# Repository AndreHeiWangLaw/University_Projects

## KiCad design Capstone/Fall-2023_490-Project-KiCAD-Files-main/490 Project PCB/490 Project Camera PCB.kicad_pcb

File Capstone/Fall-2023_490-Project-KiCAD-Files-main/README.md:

# Fall-2023_490-Project-KiCAD-Files
490 Project KiCAD Files

KiCAD doesn't really support git, be careful with your edits.
Try to only push .kd_sch files.

Don't forget to plot/trace your revision in pdf before pushing.

Before merging/rebase to your local branch, check the pdf diagrams for error. 

Don't forget to backup your local branches!

Don't forget to install the ESP32 Library under "/490 Project PCB/CAD Models/ESP32 MCUs/espressif-kicad-addon.zip"
Install it via the KiCAD Package Manager with "Install from File" button.

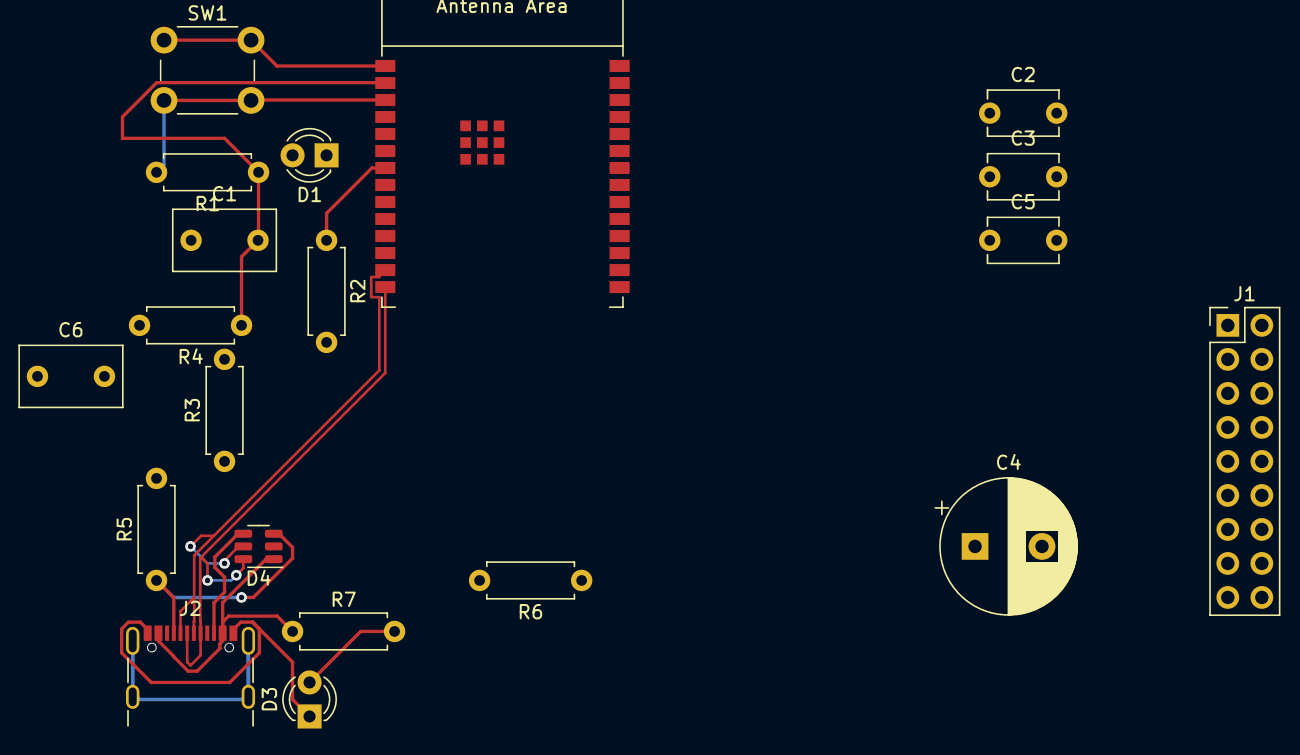
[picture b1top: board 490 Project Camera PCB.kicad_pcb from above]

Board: 2 copper layers, 20 parts (0 on the bottom side), 26 nets.

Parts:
C1, C6: 10u; C_Disc_D7.5mm_W4.4mm_P5.00mm
C2, C5: 0.1u; C_Disc_D5.1mm_W3.2mm_P5.00mm
C3: 1u; C_Disc_D5.1mm_W3.2mm_P5.00mm
C4: 100u; CP_Radial_D10.0mm_P5.00mm
D1: WP7113PGD; LED_D3.0mm
D3: WP7113VBC/D; LED_D3.0mm
D4: SP0503BAHT; SOT-23-6
J1: Conn_01x16; PinHeader_2x09_P2.54mm_Vertical
J2: Molex_2171750001; USB_C_Receptacle_GCT_USB4105-xx-A_16P_TopMnt_Horizontal
R1: 10k; R_Axial_DIN0207_L6.3mm_D2.5mm_P7.62mm_Horizontal
R2: 56R; R_Axial_DIN0207_L6.3mm_D2.5mm_P7.62mm_Horizontal
R3: 200; R_Axial_DIN0207_L6.3mm_D2.5mm_P7.62mm_Horizontal
R4: 392; R_Axial_DIN0207_L6.3mm_D2.5mm_P7.62mm_Horizontal
R5, R6: 5k1; R_Axial_DIN0207_L6.3mm_D2.5mm_P7.62mm_Horizontal
R7: 91R; R_Axial_DIN0207_L6.3mm_D2.5mm_P7.62mm_Horizontal
SW1: D6R90 F1 LFS; SW_PUSH_6mm_H7.3mm
U1: ESP32-C6-WROOM-1

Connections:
+3V3: C1.2 (-), C2.1 (+), C4.1 (+), C5.2 (-), J1.1, R1.1 (+), R3.2 (-), R4.1 (+), U1.2 (3V3)
CAMERA_DATA_1: J1.4, U1.10 (GPIO8)
CAMERA_DATA_2: J1.5, U1.15 (GPIO9)
CAMERA_DATA_3: J1.6, U1.11 (GPIO10)
CAMERA_DATA_4: J1.7, U1.12 (GPIO11)
CAMERA_DATA_5: J1.8, U1.23 (GPIO15)
CAMERA_DATA_6: J1.9, U1.16 (GPIO18)
CAMERA_DATA_7: J1.10, U1.17 (GPIO19)
CAMERA_DATA_8: J1.11, U1.18 (GPIO20)
CAMERA_HREF: J1.15, U1.27 (GPIO2/ADC1_CH2)
CAMERA_PCLK: J1.13, U1.8 (GPIO0/ADC1_CH0/XTAL_32K_P)
CAMERA_SIOC_SCL: J1.3, U1.21 (GPIO23)
CAMERA_SIOC_SDA: J1.2, U1.20 (GPIO22)
CAMERA_VSYNC: J1.12, U1.26 (GPIO3/ADC1_CH3)
CAMERA_XCLK: J1.14, U1.9 (GPIO1/ADC1_CH1/XTAL_32K_N)
GND: C1.1 (+), C2.2 (-), C3.1 (+), C4.2 (-), C5.1 (+), C6.1 (+), D1.1 (K), D3.1 (K), D4.2 (A), J1.16, J2.A1 (GND), J2.A12 (GND), J2.B1 (GND), J2.B12 (GND), R4.2 (-), R5.2 (-), R6.2 (-), SW1.1, U1.1 (GND), U1.28 (GND), U1.29 (GND)
unnamed: C3.2 (-), R1.2 (-), SW1.2, U1.3 (EN/CHIP_PU)
unnamed: C6.2 (-), R3.1 (+)
unnamed: D1.2 (A), R2.2 (-)
unnamed: D3.2 (A), R7.2 (-)
unnamed: D4.3 (K), J2.A5 (CC1), R5.1 (+)
unnamed: D4.4 (K), J2.B5 (CC2), R6.1 (+)
unnamed: R2.1 (+), U1.7 (MTDO/GPIO7)
unnamed: D4.1 (K), J2.A4 (VBUS), J2.A9 (VBUS), J2.B4 (VBUS), J2.B9 (VBUS), R7.1 (+)
USB_D+: D4.6 (K), J2.A6 (D+), J2.B6 (D+), U1.14 (GPIO13/USB_D+)
USB_D-: D4.5 (K), J2.A7 (D-), J2.B7 (D-), U1.13 (GPIO12/USB_D-)

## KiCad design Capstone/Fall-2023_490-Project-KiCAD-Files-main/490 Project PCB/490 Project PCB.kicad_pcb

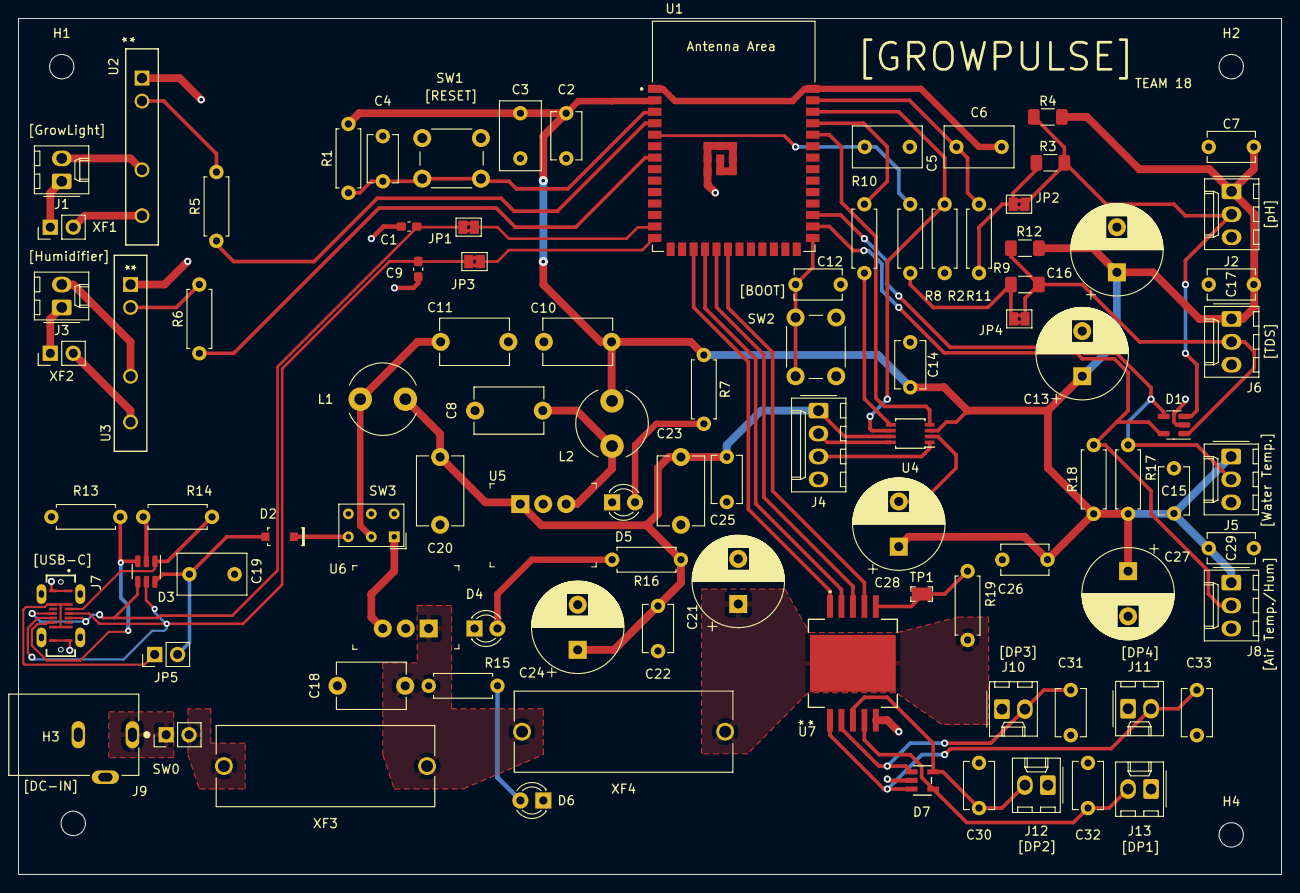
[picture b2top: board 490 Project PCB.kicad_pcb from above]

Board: 2 copper layers, 139.9 x 94.8 mm, 99 parts (0 on the bottom side), 57 nets.

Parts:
C1, C9: 47 pF; C_0603_1608Metric_Pad1.08x0.95mm_HandSolder
C2, C7, C14, C15, C17, C22, C25, C26, C29, C30, C31, C32, C33: 0.1u; C_Disc_D5.1mm_W3.2mm_P5.00mm
C3, C5, C6, C19: 10u; C_Disc_D7.5mm_W4.4mm_P5.00mm
C4, C12: 1u; C_Disc_D5.1mm_W3.2mm_P5.00mm
C8, C10, C11, C18, C20, C23: 22u; C_Disc_D7.5mm_W5.0mm_P7.50mm
C13, C16, C21, C24, C27, C28: 100u; CP_Radial_D10.0mm_P5.00mm
D1: SP0504BAHT; SOT-23-5
D2: 1N5819HW-7-F; SOD-123
D3: SP0503BAHT; SOT-23-6
D4: WP7113VBC/D; LED_D3.0mm
D5: WP7113PGD; LED_D3.0mm
D6: WP7113ID5V; LED_D3.0mm
D7: ESDA14V2SC5; SOT23-5L_STM
H1, H2, H3, H4: MountingHole; MountingHole_2.7mm_M2.5
J1, J3, J10, J11, J12, J13: Molex_0022112022; Molex_KK-254_AE-6410-02A_1x02_P2.54mm_Vertical
J2, J5, J6, J8: Molex_0022112032; Molex_KK-254_AE-6410-03A_1x03_P2.54mm_Vertical
J4: Molex_0022112042; Molex_KK-254_AE-6410-04A_1x04_P2.54mm_Vertical
J7: Molex_2171750001; GCT_USB4120-03-C_REVA
J9: PJ-102A
JP1, JP3: R0; SolderJumper-2_P1.3mm_Bridged2Bar_Pad1.0x1.5mm
JP2, JP4: SolderJumper_2_Closed; SolderJumper-2_P1.3mm_Bridged2Bar_Pad1.0x1.5mm
JP5: Jumper_VBUS_Open; PinHeader_1x02_P2.54mm_Vertical
L1, L2: 10u; L_Radial_D7.8mm_P5.00mm_Fastron_07HCP
R1, R19: 10k; R_Axial_DIN0207_L6.3mm_D2.5mm_P7.62mm_Horizontal
R2: 51k; R_Axial_DIN0207_L6.3mm_D2.5mm_P7.62mm_Horizontal
R3, R4, R9, R12: TBD; R_1206_3216Metric_Pad1.30x1.75mm_HandSolder
R5, R6: 392; R_Axial_DIN0207_L6.3mm_D2.5mm_P7.62mm_Horizontal
R7: 56R; R_Axial_DIN0207_L6.3mm_D2.5mm_P7.62mm_Horizontal
R8, R11: 1k8; R_Axial_DIN0207_L6.3mm_D2.5mm_P7.62mm_Horizontal
R10: 510; R_Axial_DIN0207_L6.3mm_D2.5mm_P7.62mm_Horizontal
R13, R14: 5k1; R_Axial_DIN0207_L6.3mm_D2.5mm_P7.62mm_Horizontal
R15: 560; R_Axial_DIN0207_L6.3mm_D2.5mm_P7.62mm_Horizontal
R16: 91R; R_Axial_DIN0207_L6.3mm_D2.5mm_P7.62mm_Horizontal
R17, R18: 4k7; R_Axial_DIN0207_L6.3mm_D2.5mm_P7.62mm_Horizontal
SW0: PH1-02-UA; PinHeader_1x02_P2.54mm_Vertical
SW1, SW2: D6R90 F1 LFS; SW_PUSH_6mm_H7.3mm
SW3: NKK_GW22LCP; SW_NKK_GW12LJP
TP1: RCT-0C; PROBE_PAD_0805
U1: ESP32-S3-WROOM-1; XCVR_ESP32-S3-WROOM-1-N8R2
U2, U3: CPC1966Y; SIP4_CPC1966Y_LTF
U4: TXB0102DCT; TSSOP-8_3x3mm_P0.65mm
U5: VX7803-1000; 3-SIP_Module_V7805-1000
U6: V7805-2000; 3-SIP_Module_V7805-1000
U7: VN340SPTR-33-E; PowerSO-10_STM
XF1, XF2: PH1-02-UA; PinHeader_1x02_P2.54mm_Vertical
XF3: 3A; FUSE_4628
XF4: 1A; FUSE_4628

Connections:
+3V3: C2.1 (+), C3.2 (-), C7.2 (-), C10.2 (-), C13.1 (+), C14.2 (-), C15.2 (-), C16.1 (+), C17.2 (-), C26.2 (-), C27.1 (+), C28.1 (+), C29.2 (-), J2.1, J5.1, J6.1, J8.1, L2.2, R1.2 (-), R4.1 (+), R7.1 (+), R12.1 (+), R17.1 (+), R18.1 (+), U1.2 (3V3), U4.3 (VCCA)
+5V: C20.2 (-), C22.2 (-), C23.2 (-), C24.1 (+), C25.2 (-), J4.1, L1.2, R16.1 (+), U4.7 (VCCB), U5.1 (Vin+)
+12V: C18.2 (-), R15.1 (+), U6.1 (Vin+), XF3.2, XF4.2
/BOOT: C12.1 (+), SW2.1, U1.27 (GPIO0/BOOT)
/EN_TXB0102D: R2.1 (+), U1.38 (GPIO2/TOUCH2/ADC1_CH1), U4.6 (OE)
/UART0RX: U1.36 (U0RXD/GPIO44/CLK_OUT2), U4.4 (A2)
/UART0TX: R10.2 (-), U1.37 (U0TXD/GPIO43/CLK_OUT1)
ADC-Sensor_pH: JP2.1 (A), R3.1 (+), R11.1 (+)
ADC-TDS_Sensor: JP4.1 (A), R8.1 (+), R9.1 (+)
GND: C1.1 (+), C2.2 (-), C3.1 (+), C4.1 (+), C5.2 (-), C6.2 (-), C7.1 (+), C8.1 (+), C9.1 (+), C10.1 (+), C11.1 (+), C12.2 (-), C13.2 (-), C14.1 (+), C15.1 (+), C16.2 (-), C17.1 (+), C18.1 (+), C19.1 (+), C20.1 (+), C21.2 (-), C22.1 (+), C23.1 (+), C24.2 (-), C25.1 (+), C26.1 (+), C27.2 (-), C28.2 (-), C29.1 (+), C30.1 (+), C31.1 (+), C32.1 (+), C33.1 (+), D1.2 (A), D3.2 (A), D4.1 (K), D5.1 (K), D6.1 (K), D7.2, J2.3, J4.4, J5.3, J6.3, J7.A1 (GND), J7.A12 (GND), J7.B1 (GND), J7.B12 (GND), J8.3, J9.2, J9.3, J10.1, J11.1, J12.1, J13.1, R2.2 (-), R13.2 (-), R14.2 (-), SW1.1, SW2.2, U1.1 (GND), U1.40 (GND), U1.41_1, U1.41_2, U1.41_3, U1.41_4, U1.41_5, U1.41_6, U1.41_7, U1.41_8, U1.41_9, U2.1, U3.1, U4.2 (GND), U5.2 (GND), U6.2 (GND), U7.5 (GND)
GPIO-Relay_Dosing_Pump_01: U1.17 (GPIO9/TOUCH9/ADC1_CH8/FSPIHD/SUBSPIHD), U7.10 (IN1)
GPIO-Relay_Dosing_Pump_02: U1.18 (GPIO10/TOUCH10/ADC1_CH9/FSPICS0/FSPIIO4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), U7.9 (IN2)
GPIO-Relay_Dosing_Pump_03: U1.19 (GPIO11/TOUCH11/ADC2_CH0/FSPID/FSPIIO5/S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), U7.8 (IN3)
GPIO-Relay_Dosing_Pump_04: U1.20 (GPIO12/TOUCH12/ADC2_CH1/FSPICLK/FSPIIO6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), U7.7 (IN4)
GPIO-Relay_Grow_Light: R5.1 (+), U1.4 (GPIO4/TOUCH4/ADC1_CH3)
GPIO-Relay_Main_Pump: R6.1 (+), U1.7 (GPIO7/TOUCH7/ADC1_CH6)
GPIO-Sensor_AirHTemp: D1.5 (K), J8.2, R18.2 (-), U1.28 (SPIIO6/GPIO35/FSPID/SUBSPID)
GPIO-Water_Temperature: D1.4 (K), J5.2, R17.2 (-), U1.29 (SPIIO7/GPIO36/FSPICLK/SUBSPICLK)
unnamed: C4.2 (-), R1.1 (+), SW1.2, U1.3 (EN)
unnamed: C5.1 (+), R8.2 (-), U1.5 (GPIO5/TOUCH5/ADC1_CH4)
unnamed: C6.1 (+), R11.2 (-), U1.39 (GPIO1/TOUCH1/ADC1_CH0)
unnamed: C8.2 (-), L2.1, U5.3 (Vo+)
unnamed: C11.2 (-), L1.1, SW3.2 (B)
unnamed: C19.2 (-), D2.A, D3.6 (K), JP5.2 (B)
unnamed: C21.1 (+), R19.1 (+), U7.EPAD (VCC), XF4.1
unnamed: D4.2 (A), R16.2 (-)
unnamed: D5.2 (A), R7.2 (-)
unnamed: D6.2 (A), R15.2 (-)
unnamed: J1.1, XF1.1 (A)
unnamed: J1.2, U2.3
unnamed: D1.3 (K), J2.2, JP2.2 (B), R3.2 (-), R4.2 (-)
unnamed: J3.1, XF2.1 (A)
unnamed: J3.2, U3.3
unnamed: J4.2, U4.8 (B1)
unnamed: J4.3, U4.1 (B2)
unnamed: D1.1 (K), J6.2, JP4.2 (B), R9.2 (-), R12.2 (-)
unnamed: D3.1 (K), J7.A5 (CC1), R14.1 (+)
unnamed: D3.3 (K), J7.B5 (CC2), R13.1 (+)
unnamed: JP1.1 (A), U1.13 (GPIO19/U1RTS/ADC2_CH8/CLK_OUT2/USB_D-)
unnamed: JP3.1 (A), U1.14 (GPIO20/U1CTS/ADC2_CH9/CLK_OUT1/USB_D+)
unnamed: J7.A4 (VBUS), J7.A9 (VBUS), J7.B4 (VBUS), J7.B9 (VBUS), JP5.1 (A)
unnamed: R5.2 (-), U2.2
unnamed: R6.2 (-), U3.2
unnamed: R10.1 (+), U4.5 (A1)
unnamed: R19.2 (-), TP1.1, U7.6 (DIAG)
unnamed: J9.1, SW0.1 (A)
unnamed: SW0.2 (B), XF3.1
unnamed: SW3.1 (A), U6.3 (Vo+)
unnamed: U2.4, XF1.2 (B)
unnamed: U3.4, XF2.2 (B)
O-PWR_Dosing_Pump_01: C33.2 (-), D7.3, J11.2, U7.1 (OUT1)
O-PWR_Dosing_Pump_02: C31.2 (-), D7.1, J10.2, U7.2 (OUT2)
O-PWR_Dosing_Pump_03: C30.2 (-), D7.5, J12.2, U7.3 (OUT3)
O-PWR_Dosing_Pump_04: C32.2 (-), D7.4, J13.2, U7.4 (OUT4)
USB_D+: C9.2 (-), D3.5 (K), J7.A6 (D+), J7.B6 (D+), JP3.2 (B)
USB_D-: C1.2 (-), D3.4 (K), J7.A7 (D-), J7.B7 (D-), JP1.2 (B)
VBUS: D2.K, SW3.3 (C)

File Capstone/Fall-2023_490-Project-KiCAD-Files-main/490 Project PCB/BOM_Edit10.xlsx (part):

Item | Reference | Description | Value | Qty | Manufacturer | MPN | Package | Type | Supplier | Supplier_PN | Price | Price Ext.
1 | C1, C9 | SMD 1608 Capacitor | 47 pF | 2 | Murata Electronics | GRM1885C1H470JA01D | 0603 (1608 Metric) | SMD | Digikey | 490-1419-2-ND | 0.18000 | 0.36
2 | C2, C7, C14, C15, C17, C22, C25, C29-C33 | THT Radial Capacitor | 0.1u | 12 | Murata Electronics | RDER71H104K0M1H03A | Radial | Tru-Hole | Digikey | 490-9144-1-ND | 0.66000 | 7.92
3 | C3, C5, C6, C19 | THT Radial Capacitor | 10u | 4 | Murata Electronics | RDEC71H106K3S1H03A | Radial | Tru-Hole | Digikey | 490-16957-1-ND | 1.47000 | 5.88
4 | C4, C12 | THT Radial Capacitor | 1u | 2 | Murata Electronics | RDER71H105K2M1H03A | Radial | Tru-Hole | Digikey | 490-9146-1-ND | 0.92000 | 1.84
5 | C8, C10, C11, C18, C20, C23 | THT CER Radial Capacitor | 22u | 6 | TDK Corporation | CC45SL3JD220JYGNA | Radial | Tru-Hole | Digikey | 445-181008-ND | 0.37000 | 2.2199999999999998
6 | C13, C16, C21, C24, C27, C28 | THT ELEC Radial Capacitor | 100u | 6 | Panasonic Electronic Components | EEU-FC1J101 | Radial | Tru-Hole | Digikey | P10343-ND | 0.85000 | 5.0999999999999996
7 | D1 | 4 Channel TVS Module: TVS DIODE 5.5VWM 8.5VC SOT23-5 | SP0504BAHT | 1 | Littelfuse Inc. | SP0504BAHTG | SOT-23-5 | SMD | Digikey | F3157TR-ND | 1.27000 | 1.27
8 | D2 | Diode 40 V 1A Surface Mount SOD-123 | 1N5819HW-7-F | 1 | Diodes Incorporated | 1N5819HW-7-F | SOD-123 | SMD | Digikey | 1N5819HW-FDICT-ND | 0.62000 | 0.62
9 | D3 | 8.5V Clamp Ipp Tvs Diode Surface Mount SOT-143-4 | SP0503BAHT | 1 | Littelfuse Inc. | SP0503BAHTG | SOT-143-4 | SMD | Digikey | F2715TR-ND | 1.24000 | 1.24
10 | D4 | LED Blue: LED BLUE CLEAR T-1 3/4 T/H | WP7113VBC/D | 1 | Kingbright | WP7113VBC/D | Radial | Tru-Hole | Digikey | 754-1807-ND | 0.80000 | 0.8
11 | D5 | LED Green: LED GREEN DIFFUSED T-1 3/4 T/H | WP7113PGD | 1 | Kingbright | WP7113PGD | Radial | Tru-Hole | Digikey | 754-1897-ND | 0.58000 | 0.57999999999999996
12 | D6 | 12V Resistor LED: LED RED CLEAR T-1 T/H | WP7113ID5V | 1 | Kingbright | WP7113ID5V | Radial | Tru-Hole | Digikey | LTH3MM12VFR4100-ND | 1.78000 | 1.78
13 | D7 | 4 Channel TVS Module: TVS DIODE 12VWM SOT23-5L | ESDA14V2SC5 | 1 | STMicroelectronics | ESDA14V2SC5 | SOT-23-5 | SMD | Digikey | 497-7744-2-ND | 1.14000 | 1.1399999999999999
14 | J1, J3, J10-J13 | Connector Header Through Hole 2 position 0.100" (2.54mm) | Molex_0022112022 | 6 | Molex | 0022112022 |  | Tru-Hole | Digikey | WM2700-ND | 0.62000 | 3.7199999999999998
15 | J2, J5, J6, J8 | Connector Header Through Hole 3 position 0.100" (2.54mm) | Molex_0022112032 | 4 | Molex | 0022112032 |  | Tru-Hole | Digikey | WM2701-ND | 0.99000 | 3.96
16 | J4 | Connector Header Through Hole 4 position 0.100" (2.54mm) | Molex_0022112042 | 1 | Molex | 0022112042 |  | Tru-Hole | Digikey | WM2702-ND | 1.02000 | 1.02
17 | J7 | USB-C (USB TYPE-C) USB 2.0 Receptacle Connector 24 (16+8 Dummy) Position Surfac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 | Molex_2130830005 | 1 | Molex | 2130830005 |  | Surface Mount, Through Hole | Digikey | 900-2130830005TR-ND | 4.8600000000000003 | 4.8600000000000003
18 | J9 | CONN PWR JACK 2X5.5MM SOLDER | PJ-102A | 1 | CUI Inc. | PJ-102A |  | Tru-Hole | Digikey | CP-102A-ND | 0.94000 | 0.94
19 | JP5 | Connector Header Through Hole 2 position 0.100" (2.54mm) | Jumper_VBUS_Open | 1 | Adam Tech | PH1-02-UA | CONN HEADER VERT 2POS 2.54MM | Tru-Hole | Digikey | 2057-PH1-02-UA-ND | 0.14000 | 0.14000000000000001
20 | L1, L2 | THT Radial Inductor | 10u | 2 | Sumida America Components Inc. | RCR875DNP-100L | Radial | Tru-Hole | Digikey | 308-2110-ND | 1.38000 | 2.76
21 | R1, R19 | THT Axial Resistor | 10k | 2 | YAGEO | CFR-25JR-10K | Axial | Tru-Hole | Digikey | 13-CFR-25JR-52-10KTR-ND | 0.15000 | 0.3
22 | R2 | THT Axial Resistor | 51k | 1 | YAGEO | CFR-25JR-51K | Axial | Tru-Hole | Digikey | 13-CFR-25JR-52-51KTR-ND | 0.15000 | 0.15
23 | R5, R6 | THT Axial Resistor | 392 | 2 | YAGEO | CFR-25JR-56R | Axial | Tru-Hole | Digikey | 13-CFR-25JR-52-56RTR-ND | 0.15000 | 0.3
24 | R7 | THT Axial Resistor | 56R | 1 | YAGEO | CFR-25JR-56R | Axial | Tru-Hole | Digikey | 13-CFR-25JR-52-56RTR-ND | 0.15000 | 0.15
25 | R8, R11 | THT Axial Resistor | 1k8 | 2 | YAGEO | CFR-25JR-1K8 | Axial | Tru-Hole | Digikey | 13-CFR-25JR-52-1K8TR-ND | 0.15000 | 0.3
26 | R10 | THT Axial Resistor | 510 | 1 | YAGEO | CFR-25JR-510R | Axial | Tru-Hole | Digikey | 13-CFR-25JR-52-510RTR-ND | 0.15000 | 0.15
27 | R13, R14 | THT Axial Resistor | 5k1 | 2 | YAGEO | CFR-25JR-5K1 | Axial | Tru-Hole | Digikey | 13-CFR-25JR-52-5K1TR-ND | 0.15000 | 0.3
28 | R15 | THT Axial Resistor | 560 | 1 | YAGEO | CFR-25JR-560R | Axial | Tru-Hole | Digikey | 13-CFR-25JR-52-560RTR-ND | 0.15000 | 0.15
29 | R16 | THT Axial Resistor | 91R | 1 | YAGEO | CFR-25JR-91R | Axial | Tru-Hole | Digikey | 13-CFR-25JR-52-91RTR-ND | 0.15000 | 0.15
30 | R17, R18 | THT Axial Resistor | 4k7 | 2 | YAGEO | CFR-25JR-4K7 | Axial | Tru-Hole | Digikey | 13-CFR-25JR-52-4K7TR-ND | 0.15000 | 0.3
31 | SW0 | Connector Header Through Hole 2 position 0.100" (2.54mm) | PH1-02-UA | 1 | Adam Tech | PH1-02-UA | CONN HEADER VERT 2POS 2.54MM | Tru-Hole | Digikey | 2057-PH1-02-UA-ND | 0.14000 | 0.14000000000000001
32 | SW1, SW2 | SWITCH PUSH SPST-NO 0.1A 32V | D6R90 F1 LFS | 2 | C&K | D6R90 F1 LFS |  | Tru-Hole | Digikey | 401-1978-ND | 2.00000 | 4
33 | SW3 | SWITCH ROCKER DPDT 0.4VA 28V | NKK_GW22LCP | 1 | NKK Switches | GW22LCP |  | Tru-Hole | Digikey | 360-2804-ND | 5.99000 | 5.99
34 | U1 | Bluetooth, WiFi 802.11b/g/n, Bluetooth v5.0 Transceiver Module 2.4GHz PCB Trace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 | ESP32-S3-WROOM-1 | 1 | Espressif | ESP32-S3-WROOM-1-N8R2 | 41-SMD Module | SMD | Digikey | 1965-ESP32-S3-WROOM-1-N4TR-ND | 4.53000 | 4.53
35 | U2, U3 | Solid State SPST-NO (1 Form A) 8-SIP, 4 Leads | CPC1966Y | 2 | IXYS Integrated Circuits Division | CPC1966Y | 4-SIP | Tru-Hole | Digikey | CLA393-ND | 6.70000 | 13.4
36 | U4 | Voltage Level Translator Bidirectional 1 Circuit 2 Channel 100Mbps 8-VSSOP | TXB0102DCT | 1 | Texas Instrument | TXB0102DCUT | 8-VSSOP | SMD | Digikey | 296-32601-2-ND | 1.63000 | 1.63
37 | U5 | Linear Regulator Replacement DC DC Converter 1 Output 3.3V 1A 6V - 36V Input | VX7803-1000 | 1 | CUI Inc. | VX7803-1000 | 3-SIP Module | Tru-Hole | Digikey | 102-4252-ND | 4.88000 | 4.88
38 | U6 | Linear Regulator Replacement DC DC Converter 1 Output 5V 2A 7V - 18V Input | V7805-2000 | 1 | CUI Inc. | V7805-1000 | 3-SIP Module | Tru-Hole | Digikey | 102-2175-ND | 14.19000 | 14.19
39 | U7 | Power Switch/Driver 1:1 N-Channel 1A 10-PowerSO | VN340SPTR-33-E | 1 | STMicroelectronics | VN340SP-33-E | 10-PowerSO | SMD | Digikey | 497-19252-ND | 9.21 | 9.2100000000000009
40 | XF1, XF2 | Connector Header Through Hole 2 position 0.100" (2.54mm) | PH1-02-UA | 2 | Adam Tech | PH1-02-UA | CONN HEADER VERT 2POS 2.54MM | Tru-Hole | Digikey | 2057-PH1-02-UA-ND | 0.14000 | 0.28000000000000003
41 | XF3 | Fuse Holder 5 A 250V 1 Circuit Cartridge Through Hole | 3A | 1 | Keystone | 4628 | 5mm x 20mm | Tru-Hole | Digikey | 36-4628-ND | 1.04000 | 1.04
42 | XF4 | Fuse Holder 5 A 250V 1 Circuit Cartridge Through Hole | 1.2A | 1 | Keystone | 4628 | 5mm x 20mm | Tru-Hole | Digikey | 36-4628-ND | 1.04000 | 1.04
 | Off-PCB Components |  |  |  |  |  |  |  |  |  | Sub-Total | 110.72999999999999
43 | XF1, XF2 | Fuse Holder 15 A 500V 1 Circuit Cartridge Free Hanging (In-Line) | 3A | 2 | MPD (Memory Protection Devices) | BF303 | 5mm x 20mm | Cartrige | Digikey | BF303-ND | 2.68 | 5.36
44 | F1, F2, F3 | 3 A 250 V AC DC Fuse Cartridge, Glass Requires Holder 5mm x 20mm | 3A | 3 | Bel Fuse Inc. | 5ST 1-R | 5mm x 20mm | Cartrige | Digikey | 507-1297-ND | 0.88 | 2.64
45 | F4 | 1 A 250 V AC DC Fuse Cartridge, Glass Requires Holder 5mm x 20mm | 1A | 1 | Bel Fuse Inc. | 5TT 3-R | 5mm x 20mm | Cartrige | Digikey | 507-1246-ND | 0.9 | 0.9
46 | Gravity™ Analog pH Kit | pH Sensor | pH Sensor | 1 | Atlas | #KIT-103P |  |  | Atlas |  | 100 | 100
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
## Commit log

2024-03-28 Create 2021W
2024-03-28 Create t
2024-08-21 Create coen311
2024-08-23 hardware
2024-08-23 machine learning
2024-08-23 website
2024-11-06 Rename README to README.md
